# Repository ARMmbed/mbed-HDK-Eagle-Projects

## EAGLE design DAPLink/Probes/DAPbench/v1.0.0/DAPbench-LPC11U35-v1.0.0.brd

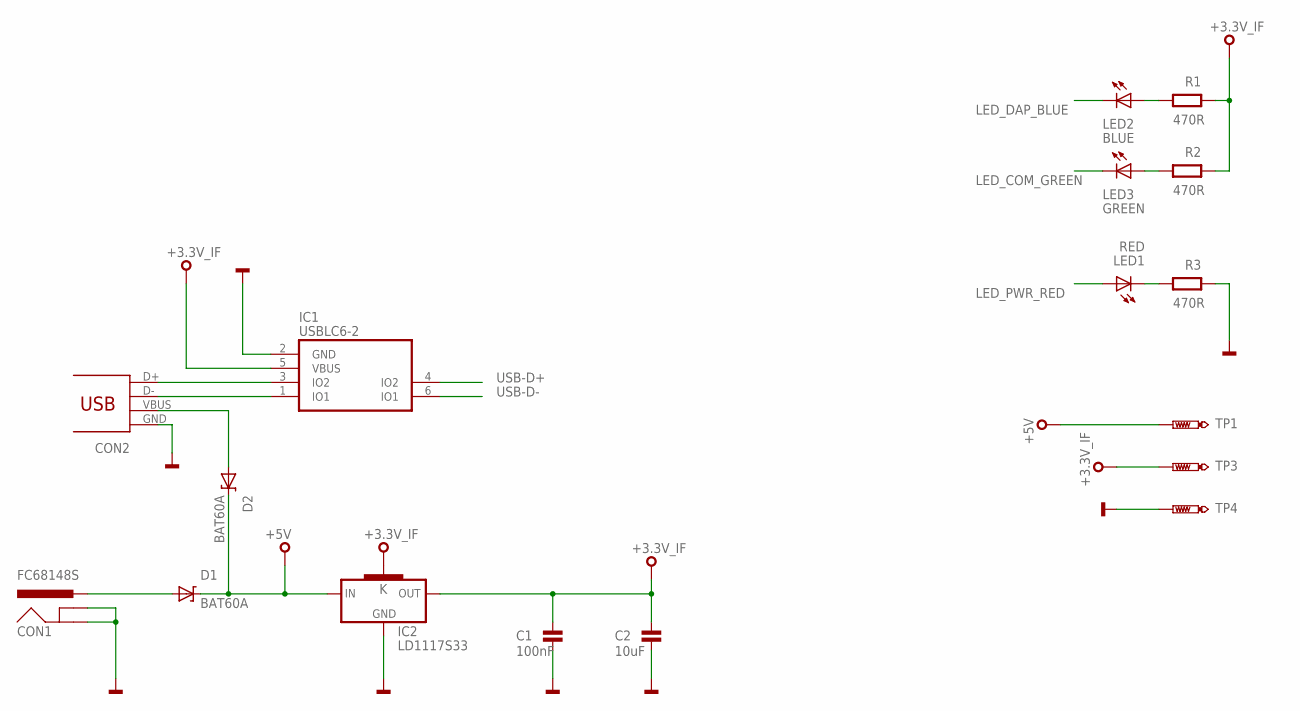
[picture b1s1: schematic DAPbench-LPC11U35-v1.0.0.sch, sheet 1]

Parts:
C1: 100nF; 0603
C2: 10uF; 0603
CON1: FC68148S
CON2: USB_MICROB; MOLEX-47364-0001
D1, D2: BAT60A; SOD323
IC1: USBLC6-2SC6; SOT23-6L
IC2: LD1117S33; SOT223
LED1: RED; CHIPLED_0603
LED2: BLUE; CHIPLED_0603
LED3: GREEN; CHIPLED_0603
R1, R2, R3: 470R; 0603@1
TP1, TP3, TP4: TEST-POINT-50R-PTH; TP50-PTH

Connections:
+3.3V_IF: C1.1, C2.1, IC1.5 (VBUS), IC2.2 (OUT), IC2.4 (K), R1.1, R2.1, TP3.TP; also elsewhere on the board
+5V: D1.K, D2.K, IC2.3 (IN), TP1.TP; also elsewhere on the board
GND: C1.2, C2.2, CON1.2 (GNDBREAK), CON1.3 (GND), CON2.GND, IC1.2 (GND), IC2.1 (GND), R3.1, TP4.TP; also elsewhere on the board
LED_COM_GREEN: LED3.C; also elsewhere on the board
LED_DAP_BLUE: LED2.C; also elsewhere on the board
LED_PWR_RED: LED1.A; also elsewhere on the board
unnamed: LED3.A, R2.2
unnamed: CON2.D-, IC1.1 (IO1)
unnamed: CON2.D+, IC1.3 (IO2)
unnamed: LED2.A, R1.2
unnamed: CON2.VBUS, D2.A
unnamed: CON1.1-1 (PWR), CON1.1-2 (PWR), D1.A
unnamed: LED1.C, R3.2
USB-D+: IC1.4 (IO2); also elsewhere on the board
USB-D-: IC1.6 (IO1); also elsewhere on the board

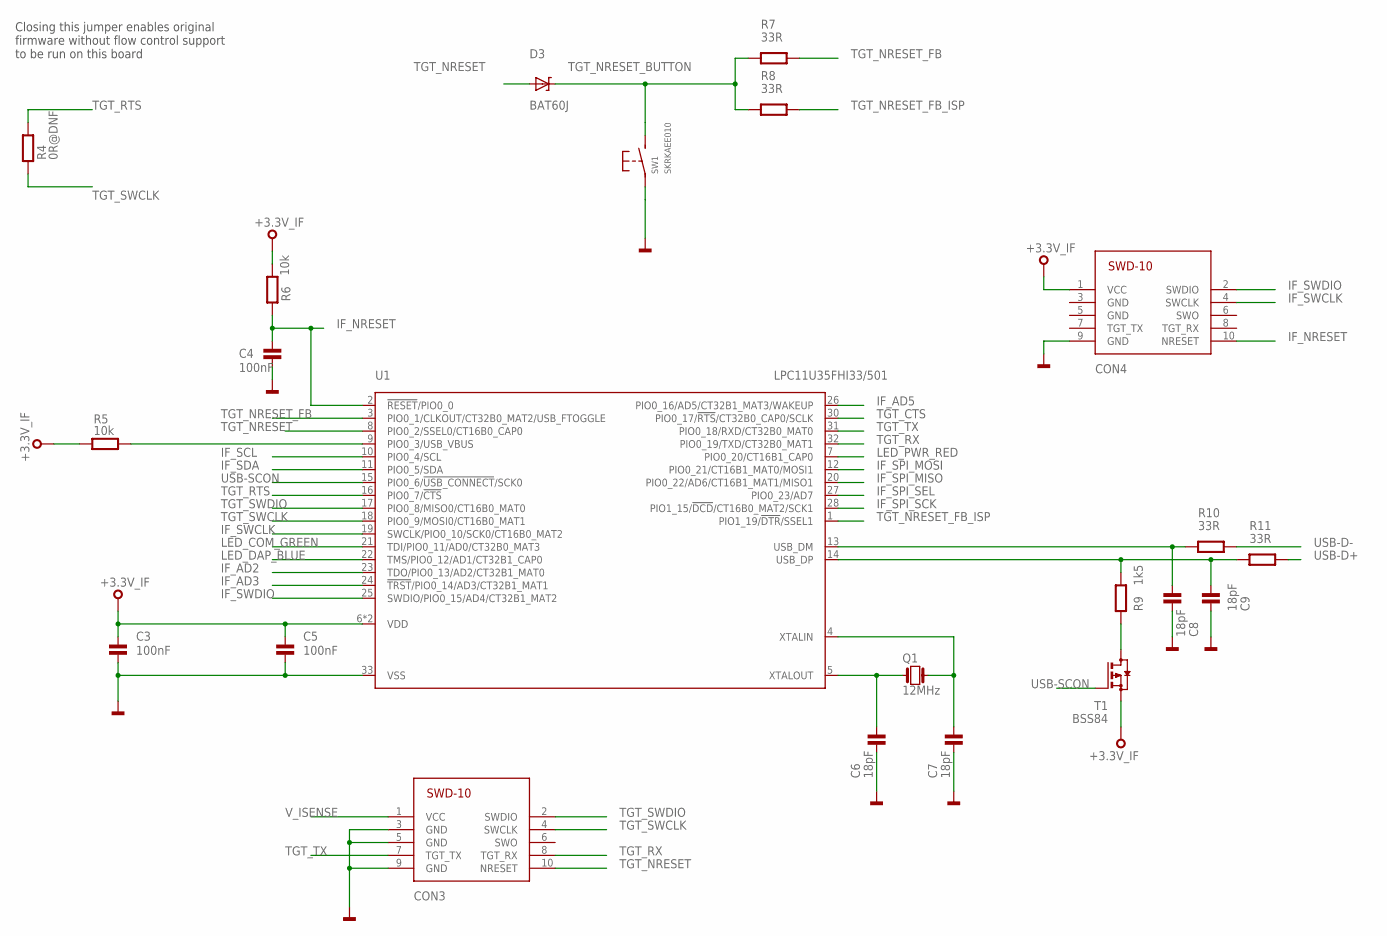
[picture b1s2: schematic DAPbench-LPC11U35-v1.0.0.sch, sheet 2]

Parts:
C3, C4, C5: 100nF; 0603
C6, C7, C8, C9: 18pF; 0603
CON3, CON4: SWD-10/TC2050_SMD; FTSH-105-02
D3: BAT60J; BAT60A
Q1: 12MHz; 3.2X.2.5
R4: 0R@DNF; 0402@1
R5, R6: 10k; 0603@1
R7, R8, R10, R11: 33R; 0603@1
R9: 1k5; 0603@1
SW1: SKRKAEE010
T1: BSS84; SOT23
U1: LPC11U35FHI33/501; SOT617-3

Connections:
+3.3V_IF: C3.1, C5.1, CON4.1 (VCC), R5.2, R6.2, T1.2 (S), U1.6 (VDD), U1.29 (VDD); also elsewhere on the board
GND: C3.2, C4.2, C5.2, C6.2, C7.2, C8.2, C9.2, CON3.3 (GND), CON3.5 (GND), CON3.9 (GND), CON4.9 (GND), SW1.P$1, U1.33 (VSS); also elsewhere on the board
IF_AD2: U1.23 (TDO/PIO0_13/AD2/CT32B1_MAT0); also elsewhere on the board
IF_AD3: U1.24 (!TRST!/PIO0_14/AD3/CT32B1_MAT1); also elsewhere on the board
IF_AD5: U1.26 (PIO0_16/AD5/CT32B1_MAT3/WAKEUP); also elsewhere on the board
IF_NRESET: C4.1, CON4.10 (NRESET), R6.1, U1.2 (!RESET!/PIO0_0)
IF_SCL: U1.10 (PIO0_4/SCL); also elsewhere on the board
IF_SDA: U1.11 (PIO0_5/SDA); also elsewhere on the board
IF_SPI_MISO: U1.20 (PIO0_22/AD6/CT16B1_MAT1/MISO1); also elsewhere on the board
IF_SPI_MOSI: U1.12 (PIO0_21/CT16B1_MAT0/MOSI1); also elsewhere on the board
IF_SPI_SCK: U1.28 (PIO1_15/!DCD!/CT16B0_MAT2/SCK1); also elsewhere on the board
IF_SPI_SEL: U1.27 (PIO0_23/AD7); also elsewhere on the board
IF_SWCLK: CON4.4 (SWCLK), U1.19 (SWCLK/PIO0_10/SCK0/CT16B0_MAT2)
IF_SWDIO: CON4.2 (SWDIO), U1.25 (SWDIO/PIO0_15/AD4/CT32B1_MAT2)
LED_COM_GREEN: U1.21 (TDI/PIO0_11/AD0/CT32B0_MAT3); also elsewhere on the board
LED_DAP_BLUE: U1.22 (TMS/PIO0_12/AD1/CT32B1_CAP0); also elsewhere on the board
LED_PWR_RED: U1.7 (PIO0_20/CT16B1_CAP0); also elsewhere on the board
unnamed: C6.1, Q1.P$1 (1), U1.5 (XTALOUT)
unnamed: C7.1, Q1.P$3 (2), U1.4 (XTALIN)
unnamed: R5.1, U1.9 (PIO0_3/USB_VBUS)
unnamed: R9.1, T1.3 (D)
TGT_CTS: U1.30 (PIO0_17/!RTS!/CT32B0_CAP0/SCLK); also elsewhere on the board
TGT_NRESET: CON3.10 (NRESET), D3.A, U1.8 (PIO0_2/SSEL0/CT16B0_CAP0); also elsewhere on the board
TGT_NRESET_BUTTON: D3.K, R7.2, R8.2, SW1.P$2 (S)
TGT_NRESET_FB: R7.1, U1.3 (PIO0_1/CLKOUT/CT32B0_MAT2/USB_FTOGGLE)
TGT_NRESET_FB_ISP: R8.1, U1.1 (PIO1_19/!DTR!/SSEL1)
TGT_RTS: R4.2, U1.16 (PIO0_7/!CTS!); also elsewhere on the board
TGT_RX: CON3.8 (TGT_RX), U1.32 (PIO0_19/TXD/CT32B0_MAT1); also elsewhere on the board
TGT_SWCLK: CON3.4 (SWCLK), R4.1, U1.18 (PIO0_9/MOSI0/CT16B0_MAT1); also elsewhere on the board
TGT_SWDIO: CON3.2 (SWDIO), U1.17 (PIO0_8/MISO0/CT16B0_MAT0); also elsewhere on the board
TGT_TX: CON3.7 (TGT_TX), U1.31 (PIO0_18/RXD/CT32B0_MAT0); also elsewhere on the board
USB-D+: R11.1; also elsewhere on the board
USB-D-: R10.1; also elsewhere on the board
USB-SCON: T1.1 (G), U1.15 (PIO0_6/!USB_CONNECT!/SCK0)
USB_DM: C8.1, R10.2, U1.13 (USB_DM)
USB_DP: C9.1, R9.2, R11.2, U1.14 (USB_DP)
V_ISENSE: CON3.1 (VCC); also elsewhere on the board

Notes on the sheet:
Closing this jumper enables original firmware without flow control support to be run on this board

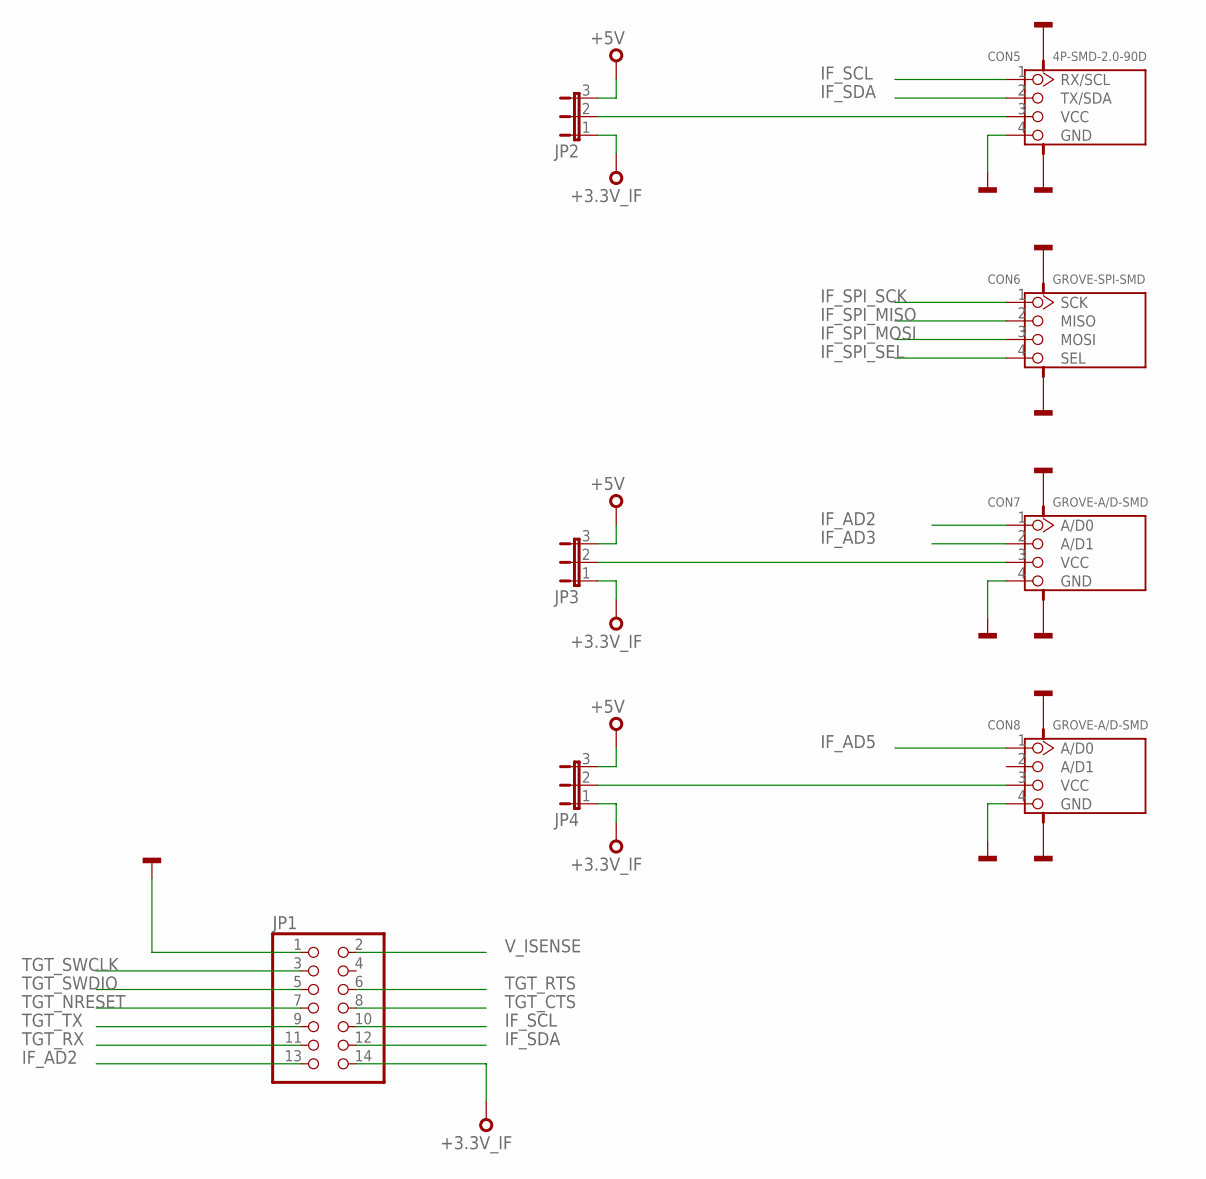
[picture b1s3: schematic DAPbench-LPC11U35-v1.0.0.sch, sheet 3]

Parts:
CON5: 4P-SMD-2.0-90D; HW4-SMD-2.0-90D
CON6: GROVE-SPI-SMD; HW4-SMD-2.0-90D
CON7, CON8: GROVE-A/D-SMD; HW4-SMD-2.0-90D
JP1: PINHD-2X7; 2X07
JP2, JP3, JP4: JP2E; JP2

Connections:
+3.3V_IF: JP1.14, JP2.1, JP3.1, JP4.1; also elsewhere on the board
+5V: JP2.3, JP3.3, JP4.3; also elsewhere on the board
GND: CON5.4 (GND), CON5.SS1, CON5.SS2, CON6.SS1, CON6.SS2, CON7.4 (GND), CON7.SS1, CON7.SS2, CON8.4 (GND), CON8.SS1, CON8.SS2, JP1.1; also elsewhere on the board
IF_AD2: CON7.1 (A/D0), JP1.13; also elsewhere on the board
IF_AD3: CON7.2 (A/D1); also elsewhere on the board
IF_AD5: CON8.1 (A/D0); also elsewhere on the board
IF_SCL: CON5.1 (RX/SCL), JP1.10; also elsewhere on the board
IF_SDA: CON5.2 (TX/SDA), JP1.12; also elsewhere on the board
IF_SPI_MISO: CON6.2 (MISO); also elsewhere on the board
IF_SPI_MOSI: CON6.3 (MOSI); also elsewhere on the board
IF_SPI_SCK: CON6.1 (SCK); also elsewhere on the board
IF_SPI_SEL: CON6.4 (SEL); also elsewhere on the board
unnamed: CON5.3 (VCC), JP2.2
unnamed: CON7.3 (VCC), JP3.2
unnamed: CON8.3 (VCC), JP4.2
TGT_CTS: JP1.8; also elsewhere on the board
TGT_NRESET: JP1.7; also elsewhere on the board
TGT_RTS: JP1.6; also elsewhere on the board
TGT_RX: JP1.11; also elsewhere on the board
TGT_SWCLK: JP1.3; also elsewhere on the board
TGT_SWDIO: JP1.5; also elsewhere on the board
TGT_TX: JP1.9; also elsewhere on the board
V_ISENSE: JP1.2; also elsewhere on the board

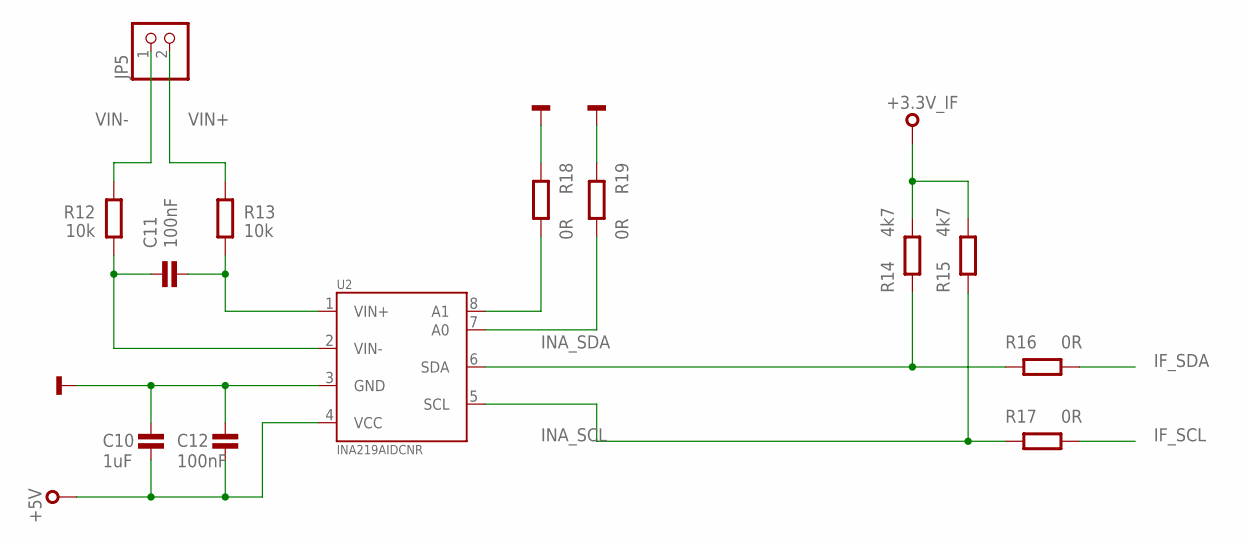
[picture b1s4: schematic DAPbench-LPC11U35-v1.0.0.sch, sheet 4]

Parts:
C10: 1uF; 0603
C11, C12: 100nF; 0603
JP5: PINHD-1X2; 1X02
R12, R13: 10k; 0603@1
R14, R15: 4k7; 0603@1
R16, R17, R18, R19: 0R; 0603@1
U2: INA219AIDCNR; SOT23-8

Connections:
+3.3V_IF: R14.1, R15.1; also elsewhere on the board
+5V: C10.2, C12.2, U2.4 (VCC); also elsewhere on the board
GND: C10.1, C12.1, R18.2, R19.2, U2.3 (GND); also elsewhere on the board
IF_SCL: R17.1; also elsewhere on the board
IF_SDA: R16.1; also elsewhere on the board
INA_SCL: R15.2, R17.2, U2.5 (SCL)
INA_SDA: R14.2, R16.2, U2.6 (SDA)
unnamed: R18.1, U2.8 (A1)
unnamed: R19.1, U2.7 (A0)
unnamed: C11.2, R12.1, U2.2 (VIN-)
unnamed: C11.1, R13.1, U2.1 (VIN+)
VIN+: JP5.2, R13.2
VIN-: JP5.1, R12.2

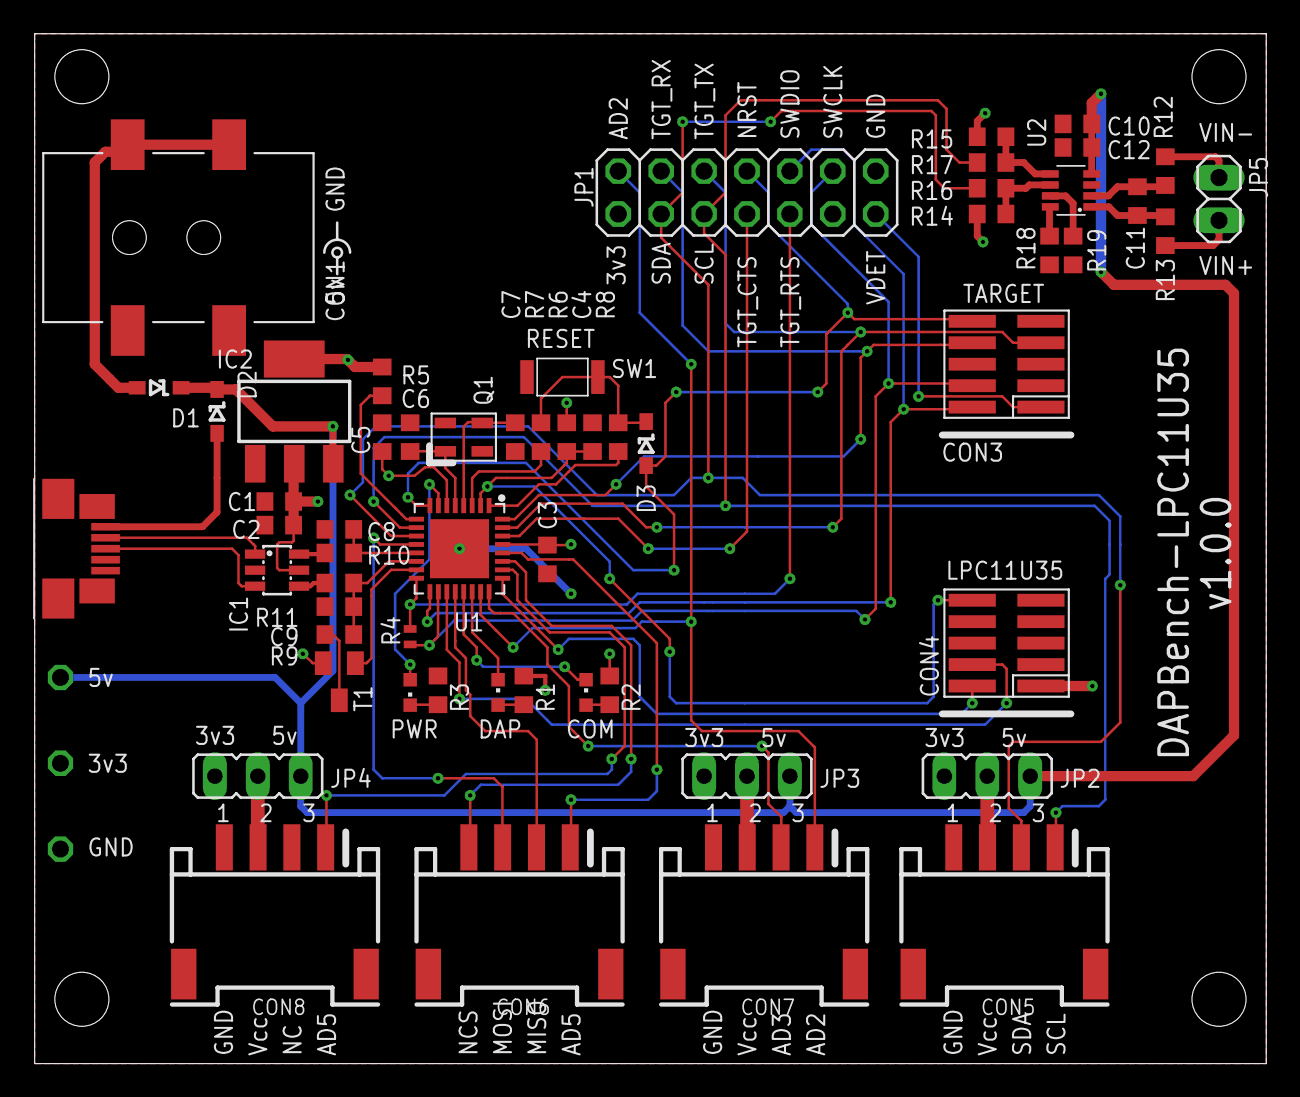
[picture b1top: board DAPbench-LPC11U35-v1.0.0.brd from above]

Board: 2 copper layers, 72.9 x 61.0 mm, 60 parts (0 on the bottom side), 56 nets.

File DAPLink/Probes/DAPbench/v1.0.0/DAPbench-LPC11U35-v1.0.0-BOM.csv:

"Qty";"Value";"Device";"Package";"Parts";"Description";"MF";"MFN";"OC-DIGIKEY";"OC-MOUSER";"OC-NEWARK";"OC_NEWARK";"VALUE";
"3";"";"JP2E";"JP2";"JP2, JP3, JP4";"JUMPER";"";"";"";"";"";"";"";
"1";"";"PINHD-1X2";"1X02";"JP5";"PIN HEADER";"";"";"";"";"";"";"";
"1";"";"PINHD-2X7";"2X07";"JP1";"PIN HEADER";"";"";"";"";"";"";"";
"4";"0R";"R0603";"0603@1";"R16, R17, R18, R19";"";"";"";"";"";"";"";"";
"1";"0R@DNF";"R0402";"0402@1";"R4";"";"";"";"";"";"";"";"";
"6";"100nF";"C0603";"0603";"C1, C3, C4, C5, C11, C12";"Capacitor";"";"";"";"";"";"";"";
"4";"10k";"R0603";"0603@1";"R5, R6, R12, R13";"";"";"";"";"";"";"";"";
"1";"10uF";"C0603";"0603";"C2";"Capacitor";"";"";"";"";"";"";"";
"1";"12MHz";"Q_3.2X2.5";"3.2X.2.5";"Q1";"";"";"";"";"";"";"";"";
"4";"18pF";"C0603";"0603";"C6, C7, C8, C9";"Capacitor";"";"";"";"";"";"";"";
"1";"1k5";"R0603";"0603@1";"R9";"";"";"";"";"";"";"";"";
"1";"1uF";"C0603";"0603";"C10";"Capacitor";"";"";"";"";"";"";"";
"4";"33R";"R0603";"0603@1";"R7, R8, R10, R11";"";"";"";"";"";"";"";"";
"3";"470R";"R0603";"0603@1";"R1, R2, R3";"";"";"";"";"";"";"";"";
"1";"4P-SMD-2.0-90D";"GROVE-UART-I2C-SMD";"HW4-SMD-2.0-90D";"CON5";"320110032";"";"";"";"";"";"";"4P-SMD-2.0-90D";
"2";"4k7";"R0603";"0603@1";"R14, R15";"";"";"";"";"";"";"";"";
"2";"BAT60A";"BAT60A";"SOD323";"D1, D2";"SCHOTTKY DIODE";"Infineon";"BAT60AE6327HTSA1";"BAT60AE6327HTSA1CT-ND";"726-BAT60AE6327";"85X4127";"";"";
"1";"BAT60J";"BAT60A";"BAT60A";"D3";"Schottky Diode";"";"";"";"";"";"";"";
"1";"BLUE";"LED0603";"CHIPLED_0603";"LED2";"SMD LED";"";"";"";"";"";"";"";
"1";"BSS84";"BSS84";"SOT23";"T1";"P-CHANNEL MOS FET";"";"";"";"";"";"";"";
"1";"FC68148S";"FC68148S";"FC68148S";"CON1";"Power Jack";"Cliff";"FC68148S";"";"";"";"1889309";"";
"1";"GREEN";"LED0603";"CHIPLED_0603";"LED3";"SMD LED";"";"";"";"";"";"";"";
"2";"GROVE-A/D-SMD";"GROVE-A/D-SMD";"HW4-SMD-2.0-90D";"CON7, CON8";"";"";"";"";"";"";"";"";
"1";"GROVE-SPI-SMD";"GROVE-SPI-SMD";"HW4-SMD-2.0-90D";"CON6";"";"";"";"";"";"";"";"";
"1";"INA219AIDCNR";"INA219AIDCNR";"SOT23-8";"U2";"Current Sense - I2C";"Texas Instruments";"INA219AIDCNR";"296-23770-1-ND";"595-INA219AIDCNR";"2295989";"";"";
"1";"LD1117S33";"LD1117S33";"SOT223";"IC2";"VOLTAGE REGULATOR SMD 3,3V";"";"";"";"";"";"";"";
"1";"LPC11U35FHI33/501";"LPC11U35FHI33/501";"SOT617-3";"U1";"32 Bit Microcontroller, ARM Cortex-M0, 50 MHz, 64 KB, 12 KB, 33 Pins, HVQFN";"NXP";"LPC11U35FHI33/501";"568-9586-ND";"771-LPC11U35FHI33501";"2115658";"";"";
"1";"RED";"LED0603";"CHIPLED_0603";"LED1";"SMD LED";"";"";"";"";"";"";"";
"1";"SKRKAEE010";"SKRKAEE010";"SKRKAEE010";"SW1";"MOMENTARY SWITCH PUSH VERTICAL (SPST)";"ALPS";"SKRKAEE010";"";"688-SKRKAE";"";"";"";
"2";"SWD-10/TC2050_SMD";"SWD-10/TC2050_SMD";"FTSH-105-02";"CON3, CON4";"1mm pitch 10-Pin Cortex Programming Header with optional TC2050 footprint solderless interchangeable";"";"";"";"";"";"";"";
"3";"TEST-POINT-50R-PTH";"TEST-POINT-50R-PTH";"TP50-PTH";"TP1, TP3, TP4";"";"";"";"";"";"";"";"";
"1";"USBLC6-2SC6";"USBLC6-2SC6";"SOT23-6L";"IC1";"";"";"";"";"";"";"";"";
"1";"USB_MICROB";"USB_MICROB";"MOLEX-47364-0001";"CON2";"USB Connectors";"";"";"";"";"";"";"";

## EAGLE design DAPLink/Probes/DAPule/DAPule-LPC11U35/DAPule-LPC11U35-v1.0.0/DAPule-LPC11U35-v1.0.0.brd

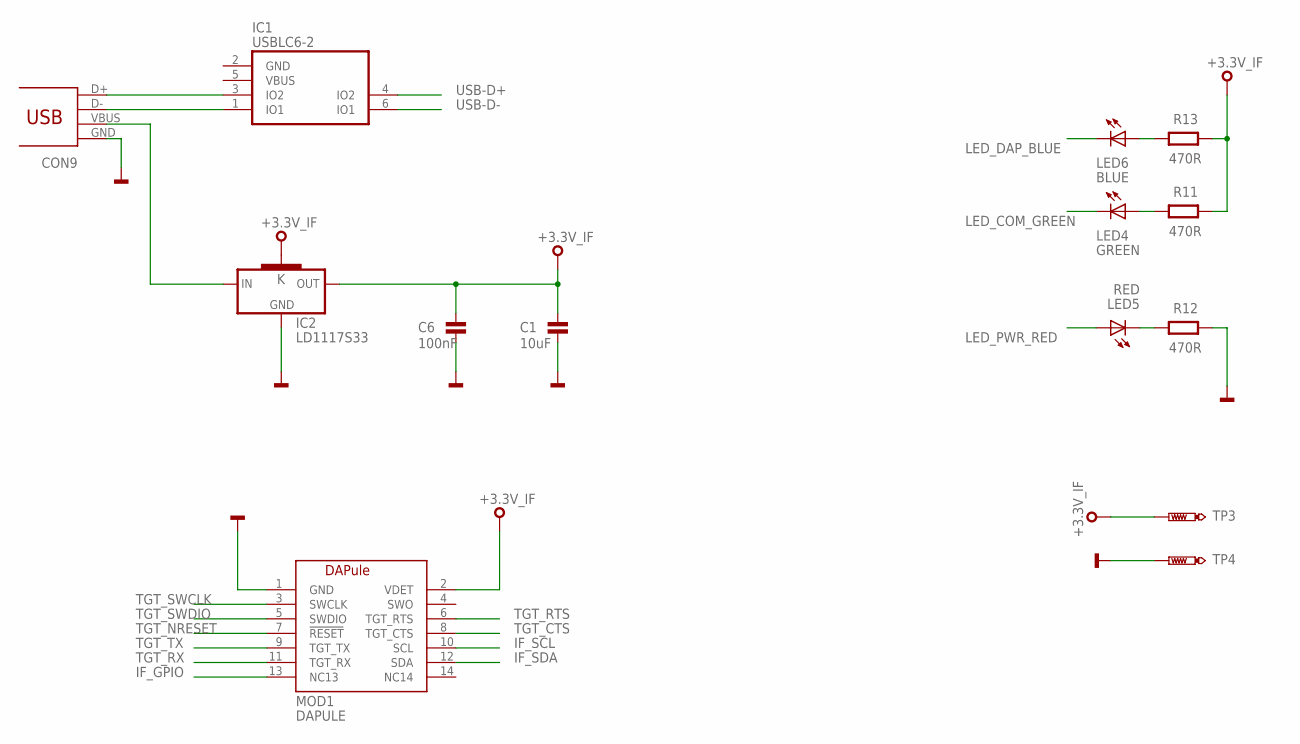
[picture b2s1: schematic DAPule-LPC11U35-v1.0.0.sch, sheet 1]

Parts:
C1: 10uF; 0603
C6: 100nF; 0603
CON9: USB_MICROB; MOLEX-47364-0001
IC1: USBLC6-2SC6; SOT23-6L
IC2: LD1117S33; SOT223
LED4: GREEN; CHIPLED_0603
LED5: RED; CHIPLED_0603
LED6: BLUE; CHIPLED_0603
MOD1: DAPULE
R11, R12, R13: 470R; 0603@1
TP3, TP4: TEST-POINT-50R-PTH; TP50-PTH

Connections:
+3.3V_IF: C1.1, C6.1, IC2.2 (OUT), IC2.4 (K), MOD1.2 (VDET), R11.1, R13.1, TP3.TP; also elsewhere on the board
GND: C1.2, C6.2, CON9.GND, IC2.1 (GND), MOD1.1 (GND), R12.1, TP4.TP; also elsewhere on the board
IF_GPIO: MOD1.13 (NC13); also elsewhere on the board
IF_SCL: MOD1.10 (SCL); also elsewhere on the board
IF_SDA: MOD1.12 (SDA); also elsewhere on the board
LED_COM_GREEN: LED4.C; also elsewhere on the board
LED_DAP_BLUE: LED6.C; also elsewhere on the board
LED_PWR_RED: LED5.A; also elsewhere on the board
unnamed: LED4.A, R11.2
unnamed: CON9.D-, IC1.1 (IO1)
unnamed: CON9.D+, IC1.3 (IO2)
unnamed: LED6.A, R13.2
unnamed: LED5.C, R12.2
unnamed: CON9.VBUS, IC2.3 (IN)
TGT_CTS: MOD1.8 (TGT_CTS); also elsewhere on the board
TGT_NRESET: MOD1.7 (!RESET); also elsewhere on the board
TGT_RTS: MOD1.6 (TGT_RTS); also elsewhere on the board
TGT_RX: MOD1.11 (TGT_RX); also elsewhere on the board
TGT_SWCLK: MOD1.3 (SWCLK); also elsewhere on the board
TGT_SWDIO: MOD1.5 (SWDIO); also elsewhere on the board
TGT_TX: MOD1.9 (TGT_TX); also elsewhere on the board
USB-D+: IC1.4 (IO2); also elsewhere on the board
USB-D-: IC1.6 (IO1); also elsewhere on the board

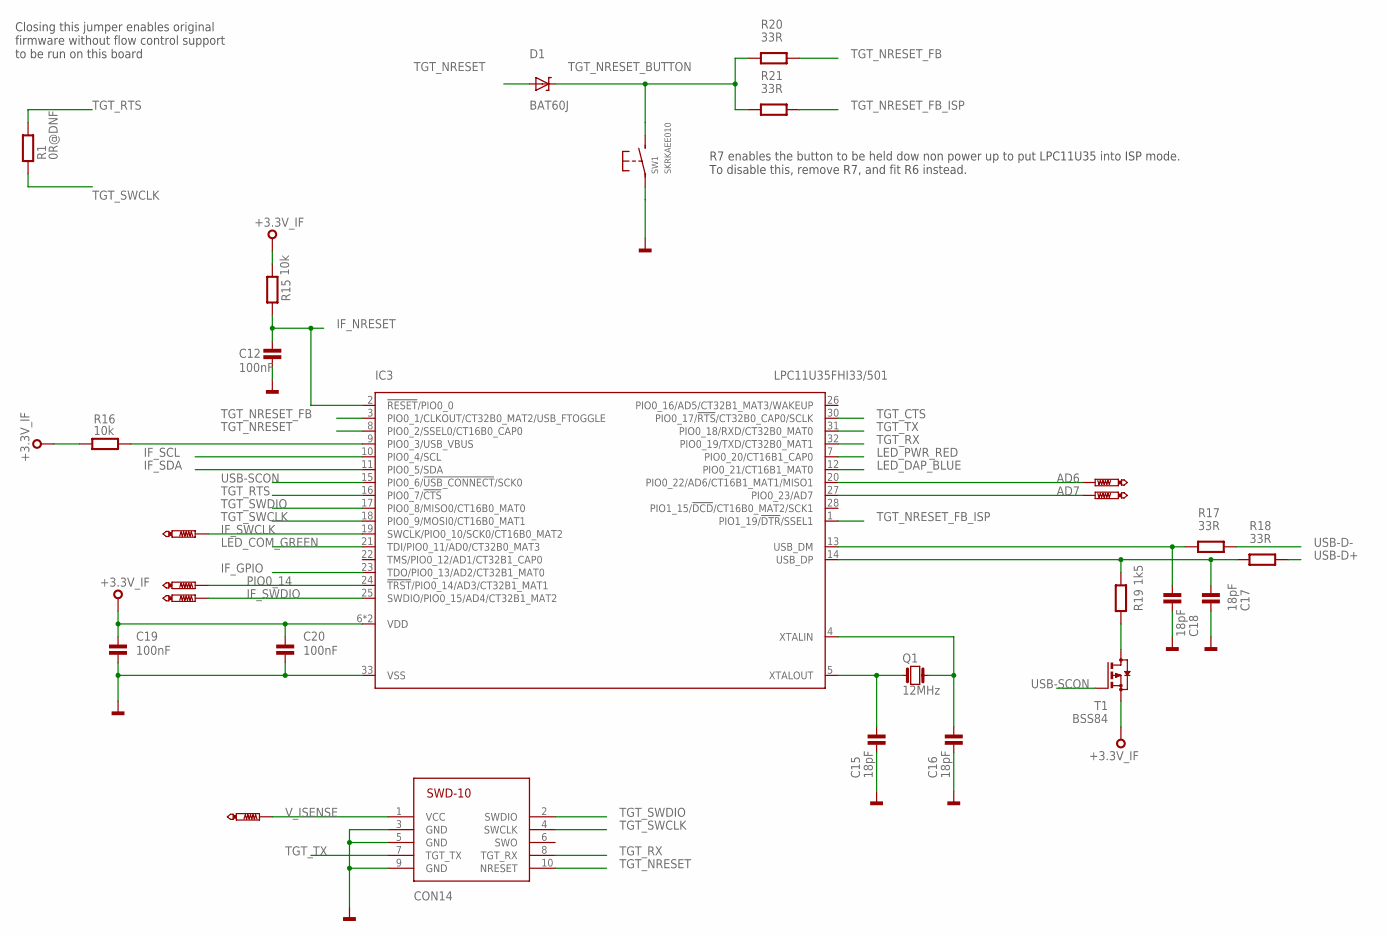
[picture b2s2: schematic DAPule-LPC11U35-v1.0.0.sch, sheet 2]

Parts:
C12, C19, C20: 100nF; 0603
C15, C16, C17, C18: 18pF; 0603
CON14: SWD-10/TC2050_SMD; FTSH-105-02
D1: BAT60J; BAT60A
IC3: LPC11U35FHI33/501; SOT617-3
Q1: 12MHz; 3.2X.2.5
R1: 0R@DNF; 0402@1
R15, R16: 10k; 0603@1
R17, R18, R20, R21: 33R; 0603@1
R19: 1k5; 0603@1
SW1: SKRKAEE010
T1: BSS84; SOT23
TP1: PTR1TP16R; TP16R
TP8, TP9, TP11, TP12, TP13: PTR1TP07R; TP07R

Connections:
+3.3V_IF: C19.1, C20.1, IC3.6 (VDD), IC3.29 (VDD), R15.2, R16.2, T1.2 (S); also elsewhere on the board
AD6: IC3.20 (PIO0_22/AD6/CT16B1_MAT1/MISO1), TP9.TP
AD7: IC3.27 (PIO0_23/AD7), TP8.TP
GND: C12.2, C15.2, C16.2, C17.2, C18.2, C19.2, C20.2, CON14.3 (GND), CON14.5 (GND), CON14.9 (GND), IC3.33 (VSS), SW1.P$1; also elsewhere on the board
IF_GPIO: IC3.23 (TDO/PIO0_13/AD2/CT32B1_MAT0); also elsewhere on the board
IF_NRESET: C12.1, IC3.2 (!RESET!/PIO0_0), R15.1
IF_SCL: IC3.10 (PIO0_4/SCL); also elsewhere on the board
IF_SDA: IC3.11 (PIO0_5/SDA); also elsewhere on the board
IF_SWCLK: IC3.19 (SWCLK/PIO0_10/SCK0/CT16B0_MAT2), TP12.TP
IF_SWDIO: IC3.25 (SWDIO/PIO0_15/AD4/CT32B1_MAT2), TP11.TP
LED_COM_GREEN: IC3.21 (TDI/PIO0_11/AD0/CT32B0_MAT3); also elsewhere on the board
LED_DAP_BLUE: IC3.12 (PIO0_21/CT16B1_MAT0); also elsewhere on the board
LED_PWR_RED: IC3.7 (PIO0_20/CT16B1_CAP0); also elsewhere on the board
unnamed: C15.1, IC3.5 (XTALOUT), Q1.P$1 (1)
unnamed: C16.1, IC3.4 (XTALIN), Q1.P$3 (2)
unnamed: IC3.9 (PIO0_3/USB_VBUS), R16.1
unnamed: R19.1, T1.3 (D)
PIO0_14: IC3.24 (!TRST!/PIO0_14/AD3/CT32B1_MAT1), TP13.TP
TGT_CTS: IC3.30 (PIO0_17/!RTS!/CT32B0_CAP0/SCLK); also elsewhere on the board
TGT_NRESET: CON14.10 (NRESET), D1.A, IC3.8 (PIO0_2/SSEL0/CT16B0_CAP0); also elsewhere on the board
TGT_NRESET_BUTTON: D1.K, R20.2, R21.2, SW1.P$2 (S)
TGT_NRESET_FB: IC3.3 (PIO0_1/CLKOUT/CT32B0_MAT2/USB_FTOGGLE), R20.1
TGT_NRESET_FB_ISP: IC3.1 (PIO1_19/!DTR!/SSEL1), R21.1
TGT_RTS: IC3.16 (PIO0_7/!CTS!), R1.2; also elsewhere on the board
TGT_RX: CON14.8 (TGT_RX), IC3.32 (PIO0_19/TXD/CT32B0_MAT1); also elsewhere on the board
TGT_SWCLK: CON14.4 (SWCLK), IC3.18 (PIO0_9/MOSI0/CT16B0_MAT1), R1.1; also elsewhere on the board
TGT_SWDIO: CON14.2 (SWDIO), IC3.17 (PIO0_8/MISO0/CT16B0_MAT0); also elsewhere on the board
TGT_TX: CON14.7 (TGT_TX), IC3.31 (PIO0_18/RXD/CT32B0_MAT0); also elsewhere on the board
USB-D+: R18.1; also elsewhere on the board
USB-D-: R17.1; also elsewhere on the board
USB-SCON: IC3.15 (PIO0_6/!USB_CONNECT!/SCK0), T1.1 (G)
USB_DM: C18.1, IC3.13 (USB_DM), R17.2
USB_DP: C17.1, IC3.14 (USB_DP), R18.2, R19.2
V_ISENSE: CON14.1 (VCC), TP1.TP

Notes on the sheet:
R7 enables the button to be held dow non power up to put LPC11U35 into ISP mode. To disable this, remove R7, and fit R6 instead.
Closing this jumper enables original firmware without flow control support to be run on this board

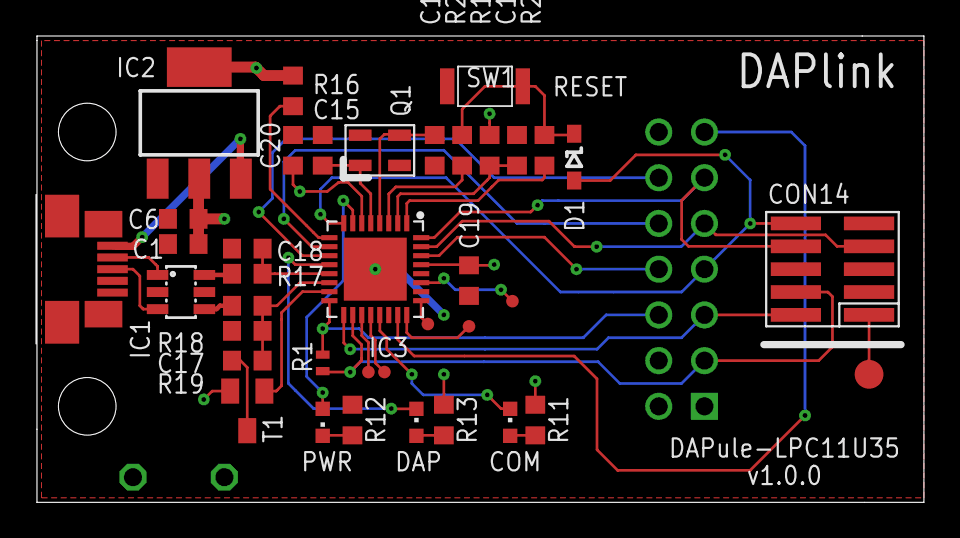
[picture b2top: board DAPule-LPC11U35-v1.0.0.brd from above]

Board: 2 copper layers, 49.3 x 25.9 mm, 41 parts (0 on the bottom side), 40 nets.

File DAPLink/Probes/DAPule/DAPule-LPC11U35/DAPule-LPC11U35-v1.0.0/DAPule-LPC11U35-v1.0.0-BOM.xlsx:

Qty | Value | Device | Package | Parts | Description
1 | 10uF | C0603 | 0603 | C1 | Capacitor
4 | 18pF | C0603 | 0603 | C15, C16, C17, C18 | Capacitor
4 | 100nF | C0603 | 0603 | C6, C12, C19, C20 | Capacitor
1 | SWD-10/TC2050_SMD | SWD-10/TC2050_SMD | FTSH-105-02 | CON14 | 1.27mm pitch 10-Pin Cortex header
1 | USB_MICROB | USB_MICROB | MOLEX-47364-0001 | CON9 | USB Connectors
1 | BAT60J | BAT60A | BAT60A | D1 | Schottky Diode
1 | USBLC6-2SC6 | USBLC6-2SC6 | SOT23-6L | IC1
1 | LD1117S33 | LD1117S33 | SOT223 | IC2 | VOLTAGE REGULATOR SMD 3,3V
1 | LPC11U35FHI33/501 | LPC11U35FHI33/501 | SOT617-3 | IC3 | 32-bit ARM Cortex-M0 MCU
1 | GREEN | LED0603 | CHIPLED_0603 | LED4 | SMD LED
1 | RED | LED0603 | CHIPLED_0603 | LED5 | SMD LED
1 | BLUE | LED0603 | CHIPLED_0603 | LED6 | SMD LED
1 | 12MHz | Q_3.2X2.5 | 3.2X.2.5 | Q1
1 | 0R@DNF | R0402 | 0402@1 | R1
3 | 470R | R0603 | 0603@1 | R11, R12, R13
2 | 10k | R0603 | 0603@1 | R15, R16
4 | 33R | R0603 | 0603@1 | R17, R18, R20, R21
1 | 1k5 | R0603 | 0603@1 | R19
1 | SKRKAEE010 | SKRKAEE010 | SKRKAEE010 | SW1 | MOMENTARY SWITCH PUSH VERTICAL (SPST)
1 | BSS84 | BSS84 | SOT23 | T1 | P-CHANNEL MOS FET

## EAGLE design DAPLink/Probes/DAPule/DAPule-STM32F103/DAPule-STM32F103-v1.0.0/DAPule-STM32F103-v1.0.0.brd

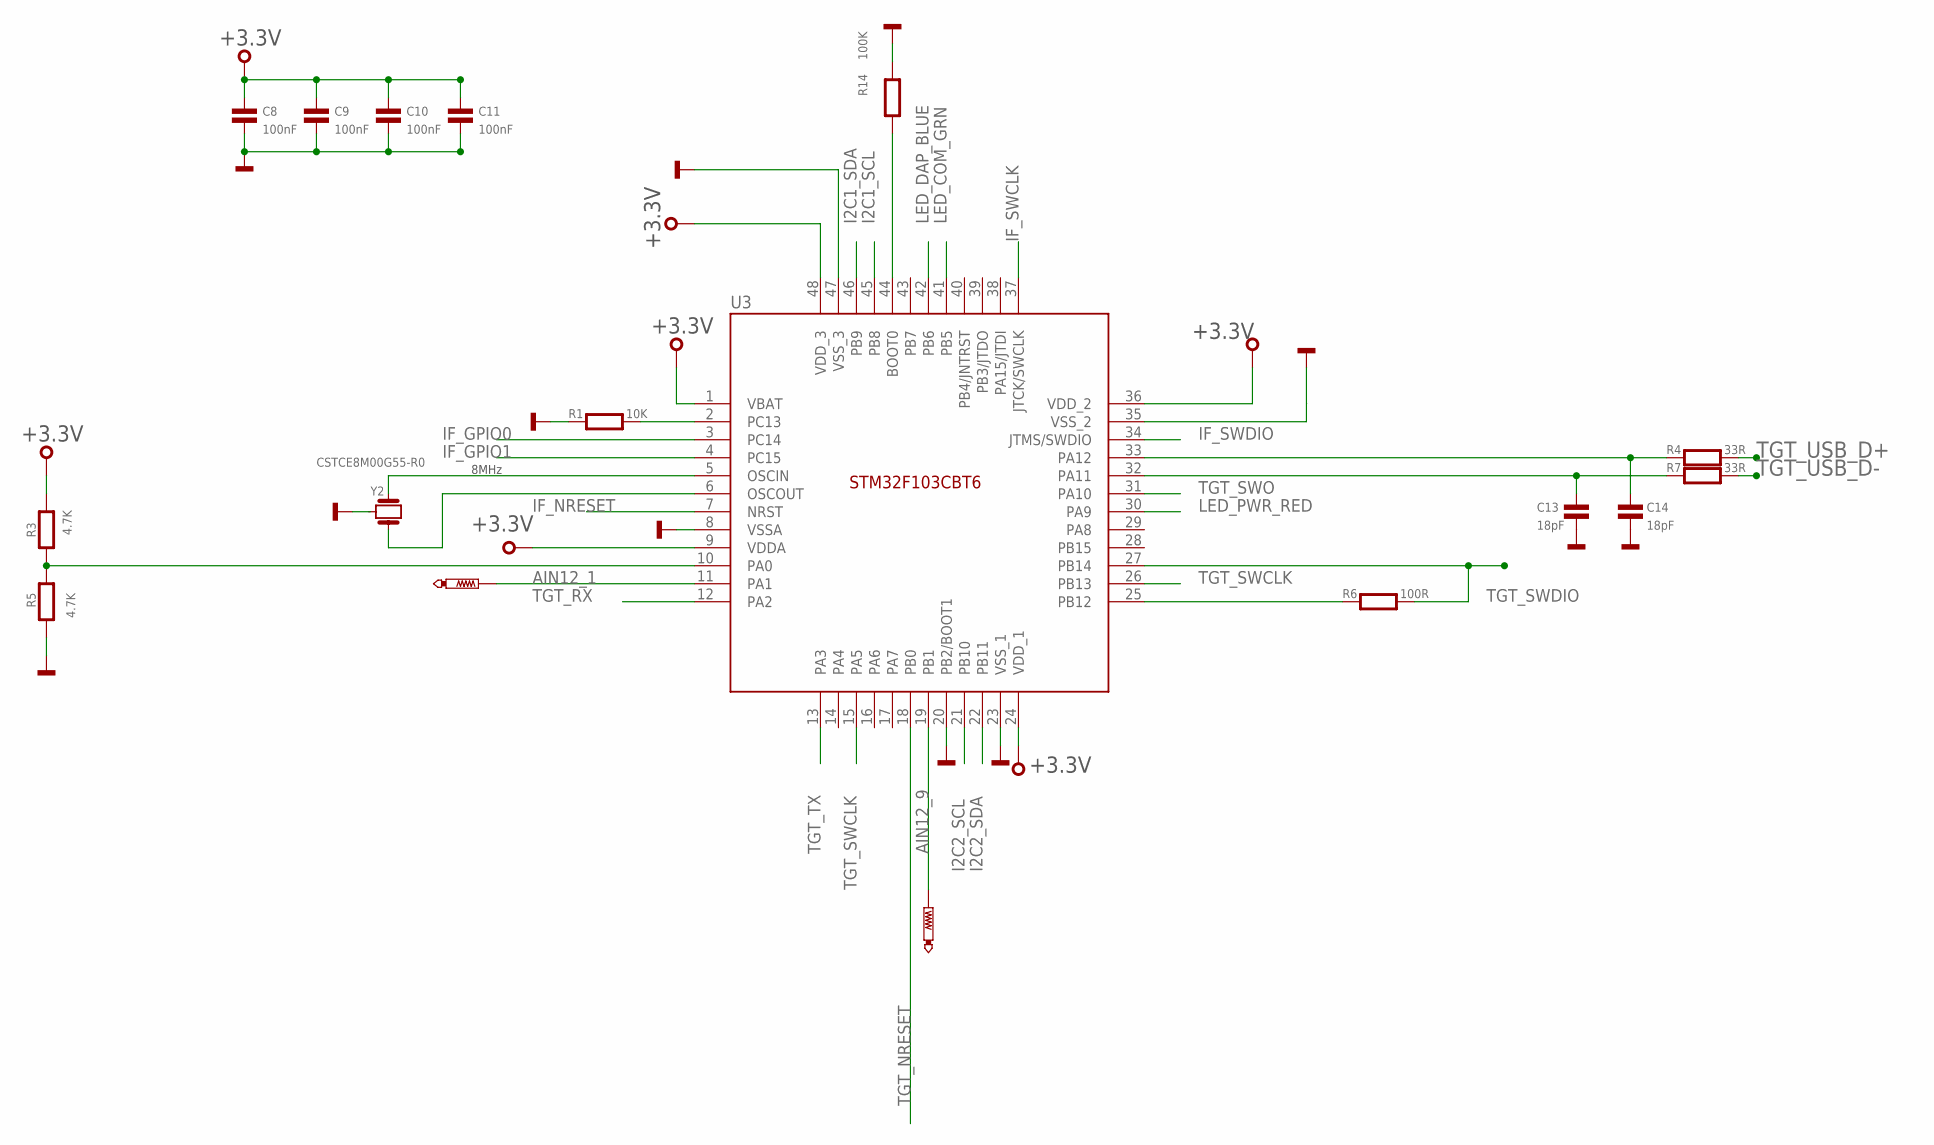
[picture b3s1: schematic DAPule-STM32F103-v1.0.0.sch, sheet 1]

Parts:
C8, C9, C10, C11: 100nF; 0603
C13, C14: 18pF; 0603
R1: 10K; 0603
R3, R5: 4.7K; 0603
R4, R7: 33R; 0603
R6: 100R; 0603
R14: 100K; 0603
TP1, TP2: PTR1TP07R; TP07R
U3: STM32F103CBT6; LQFP48
Y2: CSTCE8M00G55-R0

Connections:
+3.3V: C8.1, C9.1, C10.1, C11.1, R3.1, U3.1 (VBAT), U3.9 (VDDA), U3.24 (VDD_1), U3.36 (VDD_2), U3.48 (VDD_3); also elsewhere on the board
AIN12_1: TP2.TP, U3.11 (PA1)
AIN12_9: TP1.TP, U3.19 (PB1)
GND: C8.2, C9.2, C10.2, C11.2, C13.2, C14.2, R1.1, R5.2, R14.1, U3.8 (VSSA), U3.20 (PB2/BOOT1), U3.23 (VSS_1), U3.35 (VSS_2), U3.47 (VSS_3), Y2.2; also elsewhere on the board
I2C1_SCL: U3.45 (PB8)
I2C1_SDA: U3.46 (PB9)
I2C2_SCL: U3.21 (PB10); also elsewhere on the board
I2C2_SDA: U3.22 (PB11); also elsewhere on the board
IF_GPIO0: U3.3 (PC14); also elsewhere on the board
IF_GPIO1: U3.4 (PC15); also elsewhere on the board
IF_NRESET: U3.7 (NRST); also elsewhere on the board
IF_SWCLK: U3.37 (JTCK/SWCLK); also elsewhere on the board
IF_SWDIO: U3.34 (JTMS/SWDIO); also elsewhere on the board
LED_COM_GRN: U3.41 (PB5); also elsewhere on the board
LED_DAP_BLUE: U3.42 (PB6); also elsewhere on the board
LED_PWR_RED: U3.30 (PA9); also elsewhere on the board
unnamed: R14.2, U3.44 (BOOT0)
unnamed: R1.2, U3.2 (PC13)
unnamed: U3.6 (OSCOUT), Y2.3
unnamed: U3.5 (OSCIN), Y2.1
unnamed: R3.2, R5.1, U3.10 (PA0)
unnamed: R6.1, U3.25 (PB12)
unnamed: C14.1, R4.1, U3.33 (PA12)
unnamed: C13.1, R7.1, U3.32 (PA11)
TGT_NRESET: U3.18 (PB0); also elsewhere on the board
TGT_RX: U3.12 (PA2); also elsewhere on the board
TGT_SWCLK: U3.15 (PA5), U3.26 (PB13); also elsewhere on the board
TGT_SWDIO: R6.2, U3.27 (PB14); also elsewhere on the board
TGT_SWO: U3.31 (PA10); also elsewhere on the board
TGT_TX: U3.13 (PA3); also elsewhere on the board
TGT_USB_D+: R4.2; also elsewhere on the board
TGT_USB_D-: R7.2; also elsewhere on the board

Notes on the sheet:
8MHz
